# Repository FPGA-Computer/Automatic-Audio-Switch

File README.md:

"Automatic audio source switching"

This is the repository for this project.

Project page:
http://hw-by-design.blogspot.com/2018/08/automatic-audio-source-switching.html

Schematic tool: Eagle CAD 6.5.0
3D modelling: Sketchup 14.1 2014

The main PCB is for single sided toner transfer.  If you wish to make a double sided
PCB, just copy the ground pour from the secondardy side to primary side.  I have already
defined a ground split on tRestrict layer.

Licensing:
Schematic: Creative Commons 4.0 Attribution-ShareAlike 4.0 International
PCB & Layout: Creative Commons 4.0 Attribution-NonCommercial
3D modelling: Creative Commons 4.0 Attribution-ShareAlike 4.0 International

Creative Commons 4.0 Attribution-NonCommercial:
See http://creativecommons.org/licenses/by-nc/4.0/

Creative Commons 4.0 Attribution-ShareAlike 4.0 International
See http://creativecommons.org/licenses/by-sa/4.0/

Firmware (Keil MDK)
license: GPL 3.0

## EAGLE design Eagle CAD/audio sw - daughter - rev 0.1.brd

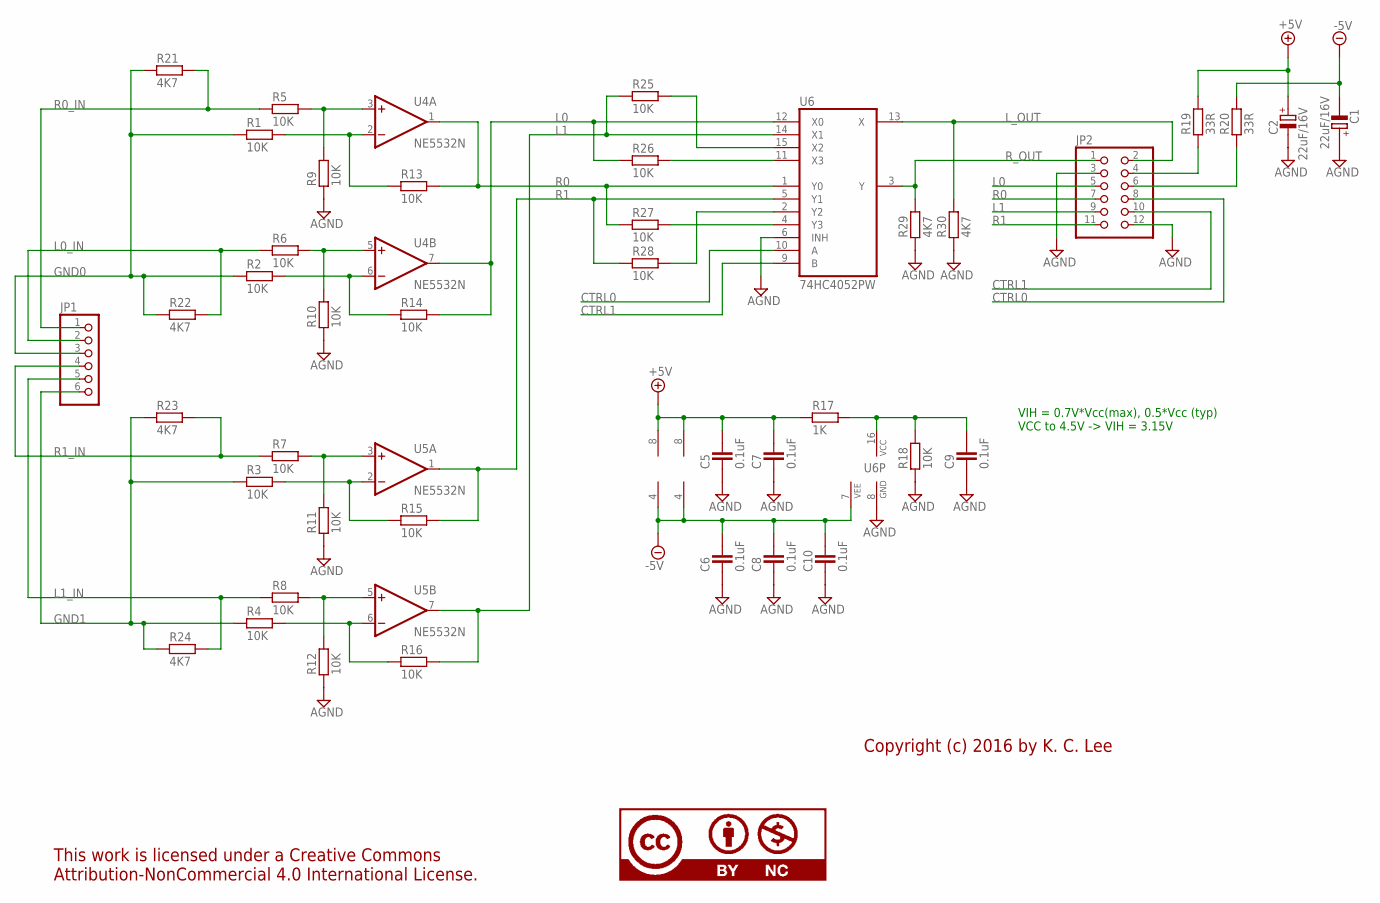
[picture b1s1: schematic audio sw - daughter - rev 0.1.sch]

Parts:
C1, C2: 22uF/16V; CAPMP6032X280N; PARTNO *
C5, C6, C7, C8, C9, C10: 0.1uF; CAPC1608X92N; PARTNO *
JP1: PINHD-1X6; 1X06; PARTNO *
JP2: PINHD-2X6_2.54; 2X06; PARTNO *
LICENSE1: CC-BY-NC75%; CC-BY-NC-75; PARTNO *
R1, R2, R3, R4, R5, R6, R7, R8, R9, R10, R11, R12, R13, R14, R15, R16, R18, R25, R26, R27, R28: 10K; RESC1608X55N; PARTNO *
R17: 1K; RESC1608X55N; PARTNO *
R19, R20: 33R; RESC2012X70N; PARTNO *
R21, R22, R23, R24, R29, R30: 4K7; RESC1608X55N; PARTNO *
U4, U5: NE5532N; SO08; PARTNO *
U6: 74HC4052PW; TSSOP16; PARTNO *

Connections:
+5V: C2.+, C5.2, C7.2, R17.1, R19.2, U4.8 (V+), U5.8 (V+)
-5V: C1.-, C6.2, C8.2, C10.2, R20.2, U4.4 (V-), U5.4 (V-), U6.7 (VEE)
AGND: C1.+, C2.-, C5.1, C6.1, C7.1, C8.1, C9.1, C10.1, JP2.3, JP2.12, R9.1, R10.1, R11.1, R12.1, R18.1, R29.1, R30.1, U6.6 (INH), U6.8 (GND)
CTRL0: JP2.8, U6.10 (A)
CTRL1: JP2.10, U6.9 (B)
GND0: JP1.3, R1.1, R2.1, R21.1, R22.1
GND1: JP1.6, R3.1, R4.1, R23.1, R24.1
L0: JP2.5, R14.2, R26.1, U4.7 (OUT), U6.12 (X0)
L0_IN: JP1.2, R6.1, R22.2
L1: JP2.9, R16.2, R25.1, U5.7 (OUT), U6.14 (X1)
L1_IN: JP1.5, R8.1, R24.2
L_OUT: JP2.2, R30.2, U6.13 (X)
unnamed: R5.2, R9.2, U4.3 (+IN)
unnamed: R1.2, R13.1, U4.2 (-IN)
unnamed: C9.2, R17.2, R18.2, U6.16 (VCC)
unnamed: R26.2, U6.11 (X3)
unnamed: R25.2, U6.15 (X2)
unnamed: R6.2, R10.2, U4.5 (+IN)
unnamed: R2.2, R14.1, U4.6 (-IN)
unnamed: JP2.4, R19.1
unnamed: R27.2, U6.4 (Y3)
unnamed: JP2.6, R20.1
unnamed: R7.2, R11.2, U5.3 (+IN)
unnamed: R3.2, R15.1, U5.2 (-IN)
unnamed: R28.2, U6.2 (Y2)
unnamed: R8.2, R12.2, U5.5 (+IN)
unnamed: R4.2, R16.1, U5.6 (-IN)
R0: JP2.7, R13.2, R27.1, U4.1 (OUT), U6.1 (Y0)
R0_IN: JP1.1, R5.1, R21.2
R1: JP2.11, R15.2, R28.1, U5.1 (OUT), U6.5 (Y1)
R1_IN: JP1.4, R7.1, R23.2
R_OUT: JP2.1, R29.2, U6.3 (Y)

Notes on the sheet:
VIH = 0.7V*Vcc(max), 0.5*Vcc (typ) VCC to 4.5V -> VIH = 3.15V
Copyright (c) 2016 by K. C. Lee

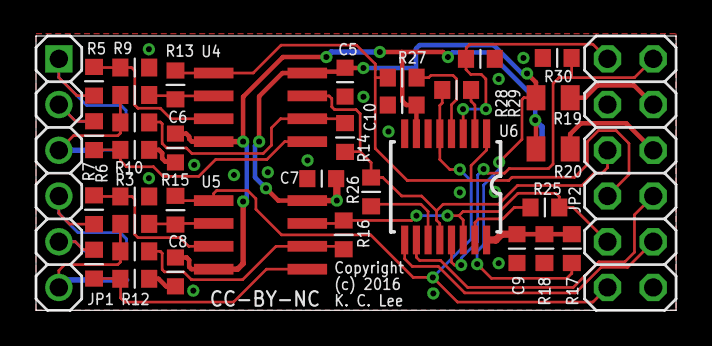
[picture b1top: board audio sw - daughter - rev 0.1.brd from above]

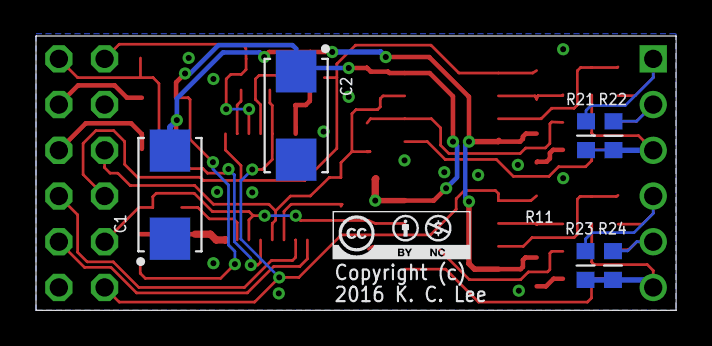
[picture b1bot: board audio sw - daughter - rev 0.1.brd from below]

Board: 2 copper layers, 35.6 x 15.2 mm, 44 parts (7 on the bottom side), 32 nets.

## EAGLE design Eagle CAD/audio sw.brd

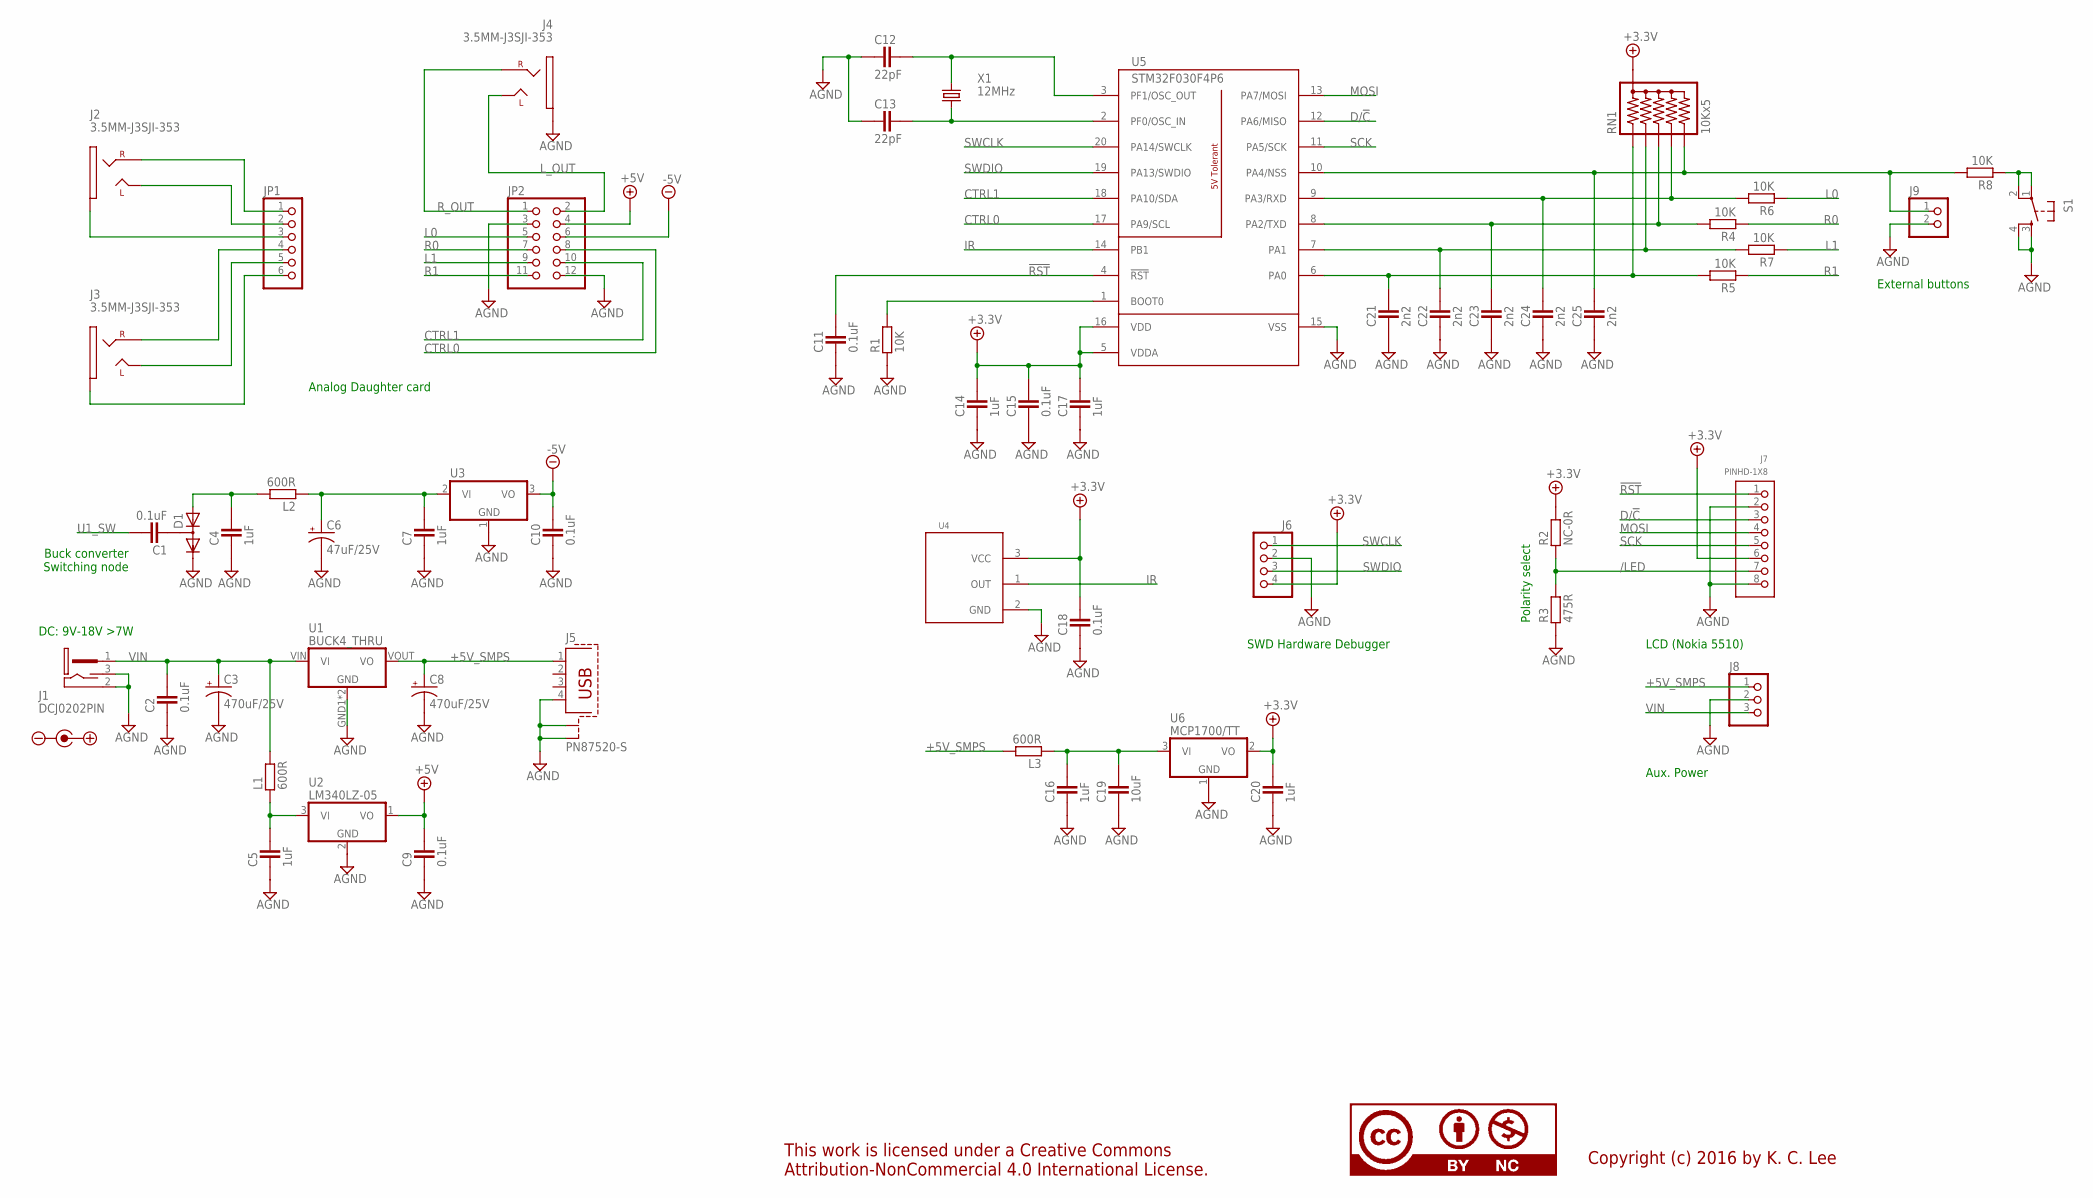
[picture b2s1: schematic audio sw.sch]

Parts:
$1_40_$: CC-BY-NC100%; CC-BY-NC-100
C1, C9, C10, C11, C15, C18: 0.1uF; CAPC1608X92N
C2: 0.1uF; CAPC2012X145AN
C3, C8: 470uF/25V; CPOL-RADIAL-470UF-25V
C4, C5, C7, C14, C16, C17, C20: 1uF; CAPC1608X92N
C6: 47uF/25V; CPOL-RADIAL-10UF-25V
C12, C13: 22pF; CAPC1608X92N
C19: 10uF; CAPC2012X145AN
C21, C22, C23, C24, C25: 2n2; CAPC1608X92N
D1: KA2KA_SOT-23; SOT95P280X135-3N
J1: DCJ0202PIN; PJ-102A
J2, J3, J4: 3.5MM-J3SJI-353; CUI-3MM
J5: PN87520-S
J6: PINHD-1X4_2.54; 1X04
J7: PINHD-1X8; 1X08
J8: PINHD-1X3; 1X03
J9: PINHD-1X2_2.54; 1X02
JP1: PINHD-1X6; 1X06
JP2: PINHD-2X6_2.54; 2X06
L1, L2, L3: 600R; RESC2012X70N
R1, R4, R5, R6, R7, R8: 10K; RESC1608X55N
R2: NC-0R; RESC1608X55N
R3: 475R; RESC1608X55N
RN1: 10Kx5; RPACK-SIP-PTH-5
S1: TAC_SWITCHPTH; TACTILE-PTH
U1: BUCK4_THRU; PWR4_THRU
U2: LM340LZ-05; TO92-CLP
U3: 79L05Z; TO92-CLP
U4: AX-1838HS; AX1838
U5: STM32F030F4P6; TSSOP20
U6: MCP1700/TT; SOT95P280X135-3N
U$1: POLARITY
X1: 12MHz; HC49U-V

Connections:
!RST: C11.2, J7.1, U5.4 (!RST)
+3.3V: C14.2, C15.2, C17.2, C18.2, C20.2, J6.4, J7.6, R2.2, RN1.P$1 (1), U4.3 (VCC), U5.5 (VDDA), U5.16 (VDD), U6.2 (VO)
+5V: C9.2, JP2.4, U2.1 (VO)
+5V_SMPS: C8.+, J5.1, J8.1, L3.2, U1.VOUT (VO)
-5V: C10.2, JP2.6, U3.3 (VO)
/LED: J7.7, R2.1, R3.2
AGND: C2.1, C3.-, C4.1, C5.1, C6.2 (-), C7.1, C8.-, C9.1, C10.1, C11.1, C12.1, C13.1, C14.1, C15.1, C16.1, C17.1, C18.1, C19.1, C20.1, C21.1, C22.1, C23.1, C24.1, C25.1, D1.2 (K), J1.2 (3), J1.3 (2), J4.1, J5.4, J5.S1, J5.S2, J6.2, J7.2, J7.8, J8.2, J9.2, JP2.3, JP2.12, R1.1, R3.1, S1.3, S1.4, U1.GND1 (GND), U1.GND2 (GND), U2.2 (GND), U3.1 (GND), U4.2 (GND), U5.15 (VSS), U6.1 (GND); also elsewhere on the board
CTRL0: JP2.8, U5.17 (PA9/SCL)
CTRL1: JP2.10, U5.18 (PA10/SDA)
D/!C: J7.3, U5.12 (PA6/MISO)
IR: U4.1 (OUT), U5.14 (PB1)
L0: JP2.5, R6.1
L1: JP2.9, R7.1
L_OUT: J4.2 (5), JP2.2
MOSI: J7.4, U5.13 (PA7/MOSI)
unnamed: C16.2, C19.2, L3.1, U6.3 (VI)
unnamed: J2.3 (2), JP1.1
unnamed 17: J2.1, JP1.3; also elsewhere on the board
unnamed: J2.2 (5), JP1.2
unnamed: J3.3 (2), JP1.4
unnamed 20: J3.1, JP1.6; also elsewhere on the board
unnamed: J3.2 (5), JP1.5
unnamed: C5.2, L1.1, U2.3 (VI)
unnamed: R8.1, S1.1, S1.2
unnamed: C6.1 (+), C7.2, L2.1, U3.2 (VI)
unnamed: C1.1, D1.3 (KA)
unnamed: C4.2, D1.1 (A), L2.2
unnamed: R1.2, U5.1 (BOOT0)
unnamed: C21.2, R5.2, RN1.P$2 (2), U5.6 (PA0)
unnamed: C22.2, R7.2, RN1.P$3 (3), U5.7 (PA1)
unnamed: C23.2, R4.2, RN1.P$4 (4), U5.8 (PA2/TXD)
unnamed: C24.2, R6.2, RN1.P$5 (5), U5.9 (PA3/RXD)
unnamed: C25.2, J9.1, R8.2, RN1.P$6 (6), U5.10 (PA4/NSS)
unnamed: C13.2, U5.2 (PF0/OSC_IN), X1.1
unnamed: C12.2, U5.3 (PF1/OSC_OUT), X1.2
R0: JP2.7, R4.1
R1: JP2.11, R5.1
R_OUT: J4.3 (2), JP2.1
SCK: J7.5, U5.11 (PA5/SCK)
SWCLK: J6.1, U5.20 (PA14/SWCLK)
SWDIO: J6.3, U5.19 (PA13/SWDIO)
U1_SW: C1.2
VIN: C2.2, C3.+, J1.1, J8.3, L1.2, U1.VIN (VI)

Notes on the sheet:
Buck converter Switching node
DC: 9V-18V >7W
Polarity select
External buttons
SWD Hardware Debugger
Aux. Power
LCD (Nokia 5510)
Copyright (c) 2016 by K. C. Lee
Analog Daughter card

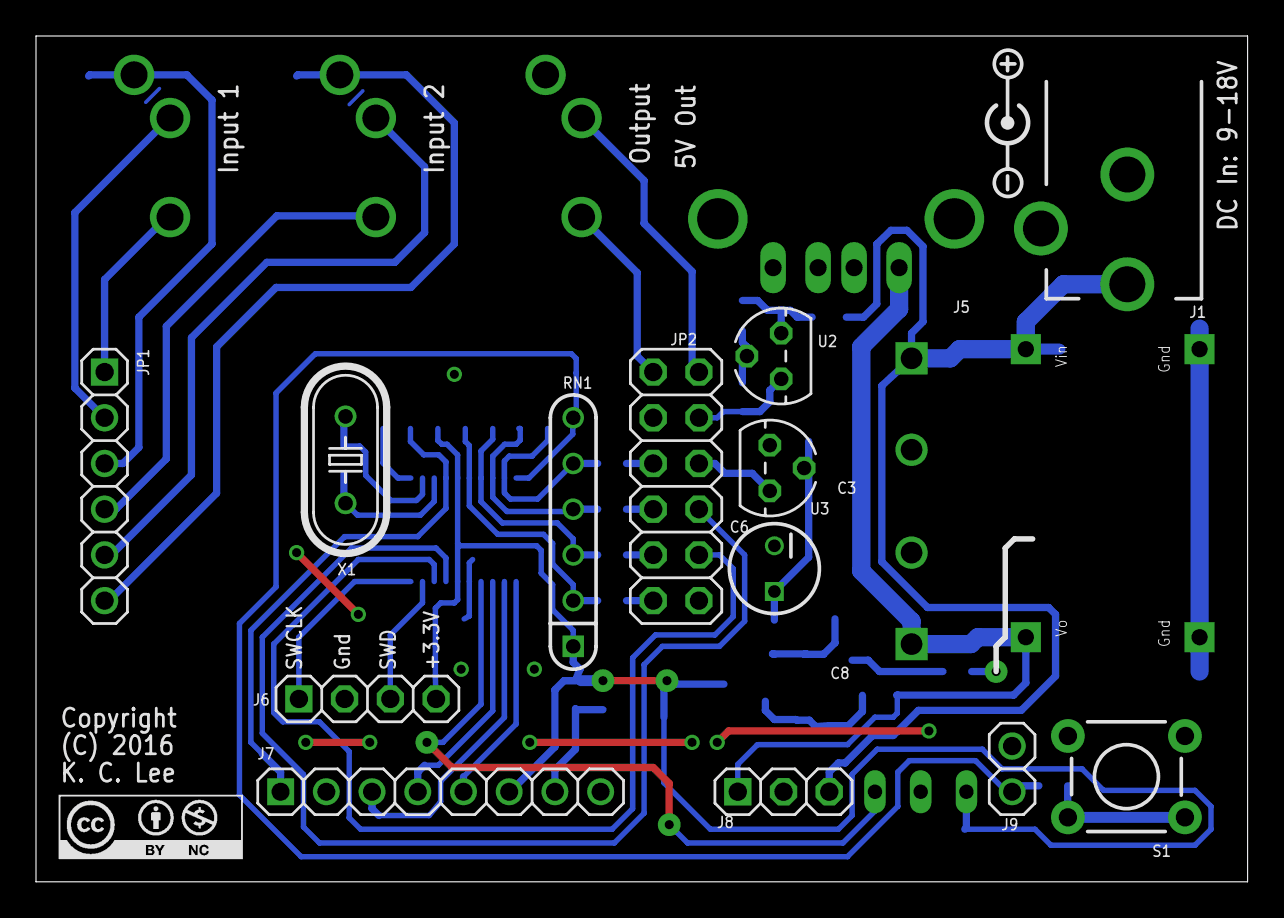
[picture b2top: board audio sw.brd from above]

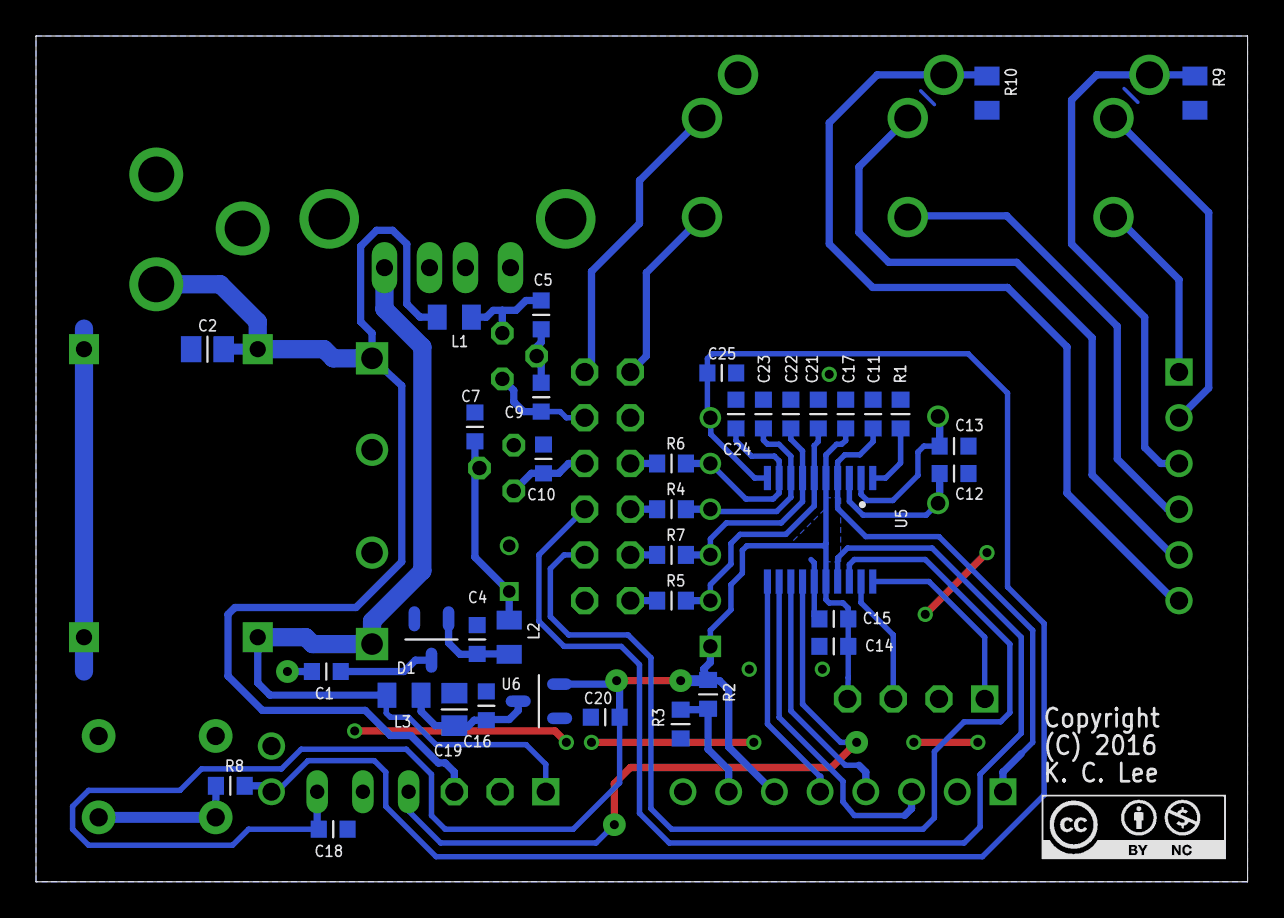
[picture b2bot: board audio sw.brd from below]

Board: 2 copper layers, 67.3 x 47.0 mm, 62 parts (39 on the bottom side), 42 nets.

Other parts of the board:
LICENSE1: CC-BY-NC100%; CC-BY-NC-100
R9: 0R; RESC2012X70N
R10: NC-0R; RESC2012X70N

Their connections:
AGND: R9.2, R10.2; also elsewhere on the board
unnamed 17: R9.1; also elsewhere on the board
unnamed 20: R10.1; also elsewhere on the board

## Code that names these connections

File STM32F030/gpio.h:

/*
 * gpio.h
 *
 * Created: March-12-16, 5:37:11 PM
 *  Author: K. C. Lee
 * Copyright (c) 2016 by K. C. Lee 
 
 	This program is free software: you can redistribute it and/or modify
	it under the terms of the GNU General Public License as published by
	the Free Software Foundation, either version 3 of the License, or
	(at your option) any later version.

	This program is distributed in the hope that it will be useful,
	but WITHOUT ANY WARRANTY; without even the implied warranty of
	MERCHANTABILITY or FITNESS FOR A PARTICULAR PURPOSE.  See the
	GNU General Public License for more details.

	You should have received a copy of the GNU General Public License
	along with this program.

	If not, see http://www.gnu.org/licenses/gpl-3.0.en.html
 */ 

#ifndef _GPIO_H_
#define _GPIO_H_

// STM32F030F4 GPIO

enum GPIO_A_PINS
{ 
	PA0,PA1,PA2,PA3,PA4,PA5,PA6,PA7,
  PA9=9,PA10=10,PA13=13,PA14=14
};

enum GPIO_B_PINS
{	
	PB1=1
};

enum GPIO_F_PINS
{
	PF0,PF1
};

#define PIN_F2(BIT,FUNC) 		((FUNC)<<(BIT*2))

// MODER
#define PIN_MODER_MASK(BIT)		PIN_F2(BIT,0x03)
#define PIN_ANALOG(BIT)				PIN_F2(BIT,0x03)
#define PIN_INPUT(BIT)				PIN_F2(BIT,0x00)
#define PIN_OUTPUT(BIT)				PIN_F2(BIT,0x01)
#define PIN_ALT(BIT)					PIN_F2(BIT,0x02)

// AFR[0]
#define PIN_AFRL(BIT,AF)			(AF<<((BIT)*4))
// AFR[1]
#define PIN_AFRH(BIT,AF)			PIN_AFRL(BIT-8,AF)

// OSPEEDR
#define PIN_OSPEED(BIT,SPEED) PIN_F2(BIT,SPEED)

// OTYPER
#define PIN_PUSHPULL(BIT)			0
#define PIN_OPENDRAIN(BIT)		(1<<BIT)

// PUPDR
#define PIN_PULLUP(BIT)				PIN_F2(BIT,0x01)
#define PIN_PULLDOWN(BIT)			PIN_F2(BIT,0x02)

// BSRR
#define PIN_SET(BIT)					(1<<BIT)
#define PIN_CLR(BIT)					(1<<(BIT+16))
#endif

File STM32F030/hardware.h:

/*
 * hardware.h
 *
 * Created: March-14-16, 4:52:17 PM
 *  Author: K. C. Lee
 * Copyright (c) 2016 by K. C. Lee 
 
 	This program is free software: you can redistribute it and/or modify
	it under the terms of the GNU General Public License as published by
	the Free Software Foundation, either version 3 of the License, or
	(at your option) any later version.

	This program is distributed in the hope that it will be useful,
	but WITHOUT ANY WARRANTY; without even the implied warranty of
	MERCHANTABILITY or FITNESS FOR A PARTICULAR PURPOSE.  See the
	GNU General Public License for more details.

	You should have received a copy of the GNU General Public License
	along with this program.

	If not, see http://www.gnu.org/licenses/gpl-3.0.en.html
 */ 

#ifndef _HARDWARE_H_
#define _HARDWARE_H_

#include "main.h"
#include "gpio.h"

#define CPU_CLOCK					48000000UL
#define UART_BAUD					115200

#define HSE_CLOCK					12000000UL
#define HSE
#define HSE_BYPASS				0

// Enable Debug shell 
//#define DBG_SHELL
#undef DBG_SHELL

//#define ADC_RES_8
#define ADC_RES_12

// 12MHz clock x4 = 48MHz
#define CFGR_PLL_MULT					RCC_CFGR_PLLMUL4

#define LCD_DC								PA6
#define ADC_SRC_GROUP					(ADC_CHSELR_CHSEL0|ADC_CHSELR_CHSEL1|ADC_CHSELR_CHSEL2|ADC_CHSELR_CHSEL3|ADC_CHSELR_CHSEL4)

#define PEAK_DECAY_SAMPLES		((PEAK_VOLUME_DECAY*ADC_SAMPLE_RATE/ADC_BLOCK_SIZE)/1000)
#define ADC_AVERAGES					(VOLUME_AVERAGE_PERIOD*ADC_SAMPLE_RATE/ADC_BLOCK_SIZE/1000)

// Max # of audio source
#define ADC_MAX_SRC						2
// L/R channels
#define ADC_CH_PER_SRC				2
#define ADC_MAX_AUD_CH				(ADC_MAX_SRC*ADC_CH_PER_SRC)
// Max # of channels per conversion
#define ADC_MAX_CH						(ADC_MAX_AUD_CH+1)

#include "main.h"
#include "nokia5110.h"
#include "adc.h"
#include "audio.h"
#include "fifo.h"
#include "rtc.h"
#include "IR Remote.h"

void Hardware_Init(void);

enum ADC_Chs
{
	Audio_R1, Audio_L1, Audio_R0, Audio_L0, Buttons
};

#define IR_PORT			GPIOB
#define IR_PIN			PB1
#define IR_INP			(IR_PORT->IDR & (1<<IR_PIN))			

#define GPIOA_MODER (PIN_ALT(PA14)|PIN_ALT(PA13)|				/* SWCLK, SWDIO */	\
										 PIN_OUTPUT(PA10)|PIN_OUTPUT(PA9)|	/* CTRL1, CTRL0	*/	\
										 PIN_ALT(PA7)|PIN_OUTPUT(PA6)|			/* MOSI, D/C 		*/	\
										 PIN_ALT(PA5)|PIN_ANALOG(PA4)|			/* SCK ???			*/	\
										 PIN_ANALOG(PA3)|PIN_ANALOG(PA2)|		/* L0, R0				*/	\
		                 PIN_ANALOG(PA1)|PIN_ANALOG(PA0))		/* L1, R1				*/
										 
#define CTRL1				PA10
#define CTRL0				PA9

#define GPIOA_AFR1	 0


#endif

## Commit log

2016-07-05 Initial commit - add mainboard schematic/PCB
2016-07-05 layout - removed via restrict mask obscuring layout
2016-07-12 Added daughter card files and Sketchup 3D models
2016-08-17 Firmware - pre-release
2016-08-19 Relay version - initial bug fix - remove old files
    Relay version - initial bug fix1 - update new files
    Relay version - initial bug fix2 - remove non-source
2016-08-22 Relay version - added Audio switching, bug fixes, updates Minor tweak for noisy relay circuit Bug fix - wrong define constants used. :( Change alti-alias filter to 18kHz + cleanup Update CAD files Up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
2016-08-30 Tweaks for daughtercard Hardware updates
2016-09-05 Enable Loudness Protection + BOM Consolidation
2016-09-08 bin search lookup, new plot routines - back port
2018-08-02 Project hosting change

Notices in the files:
parts and their libraries:
Misc logo: This work is licensed under a Creative Commons
Attribution-NonCommercial 4.0 International License.
SparkFun-Passives: Licensing: Creative Commons ShareAlike 4.0 International - https://creativecommons.org/licenses/by-sa/4.0
